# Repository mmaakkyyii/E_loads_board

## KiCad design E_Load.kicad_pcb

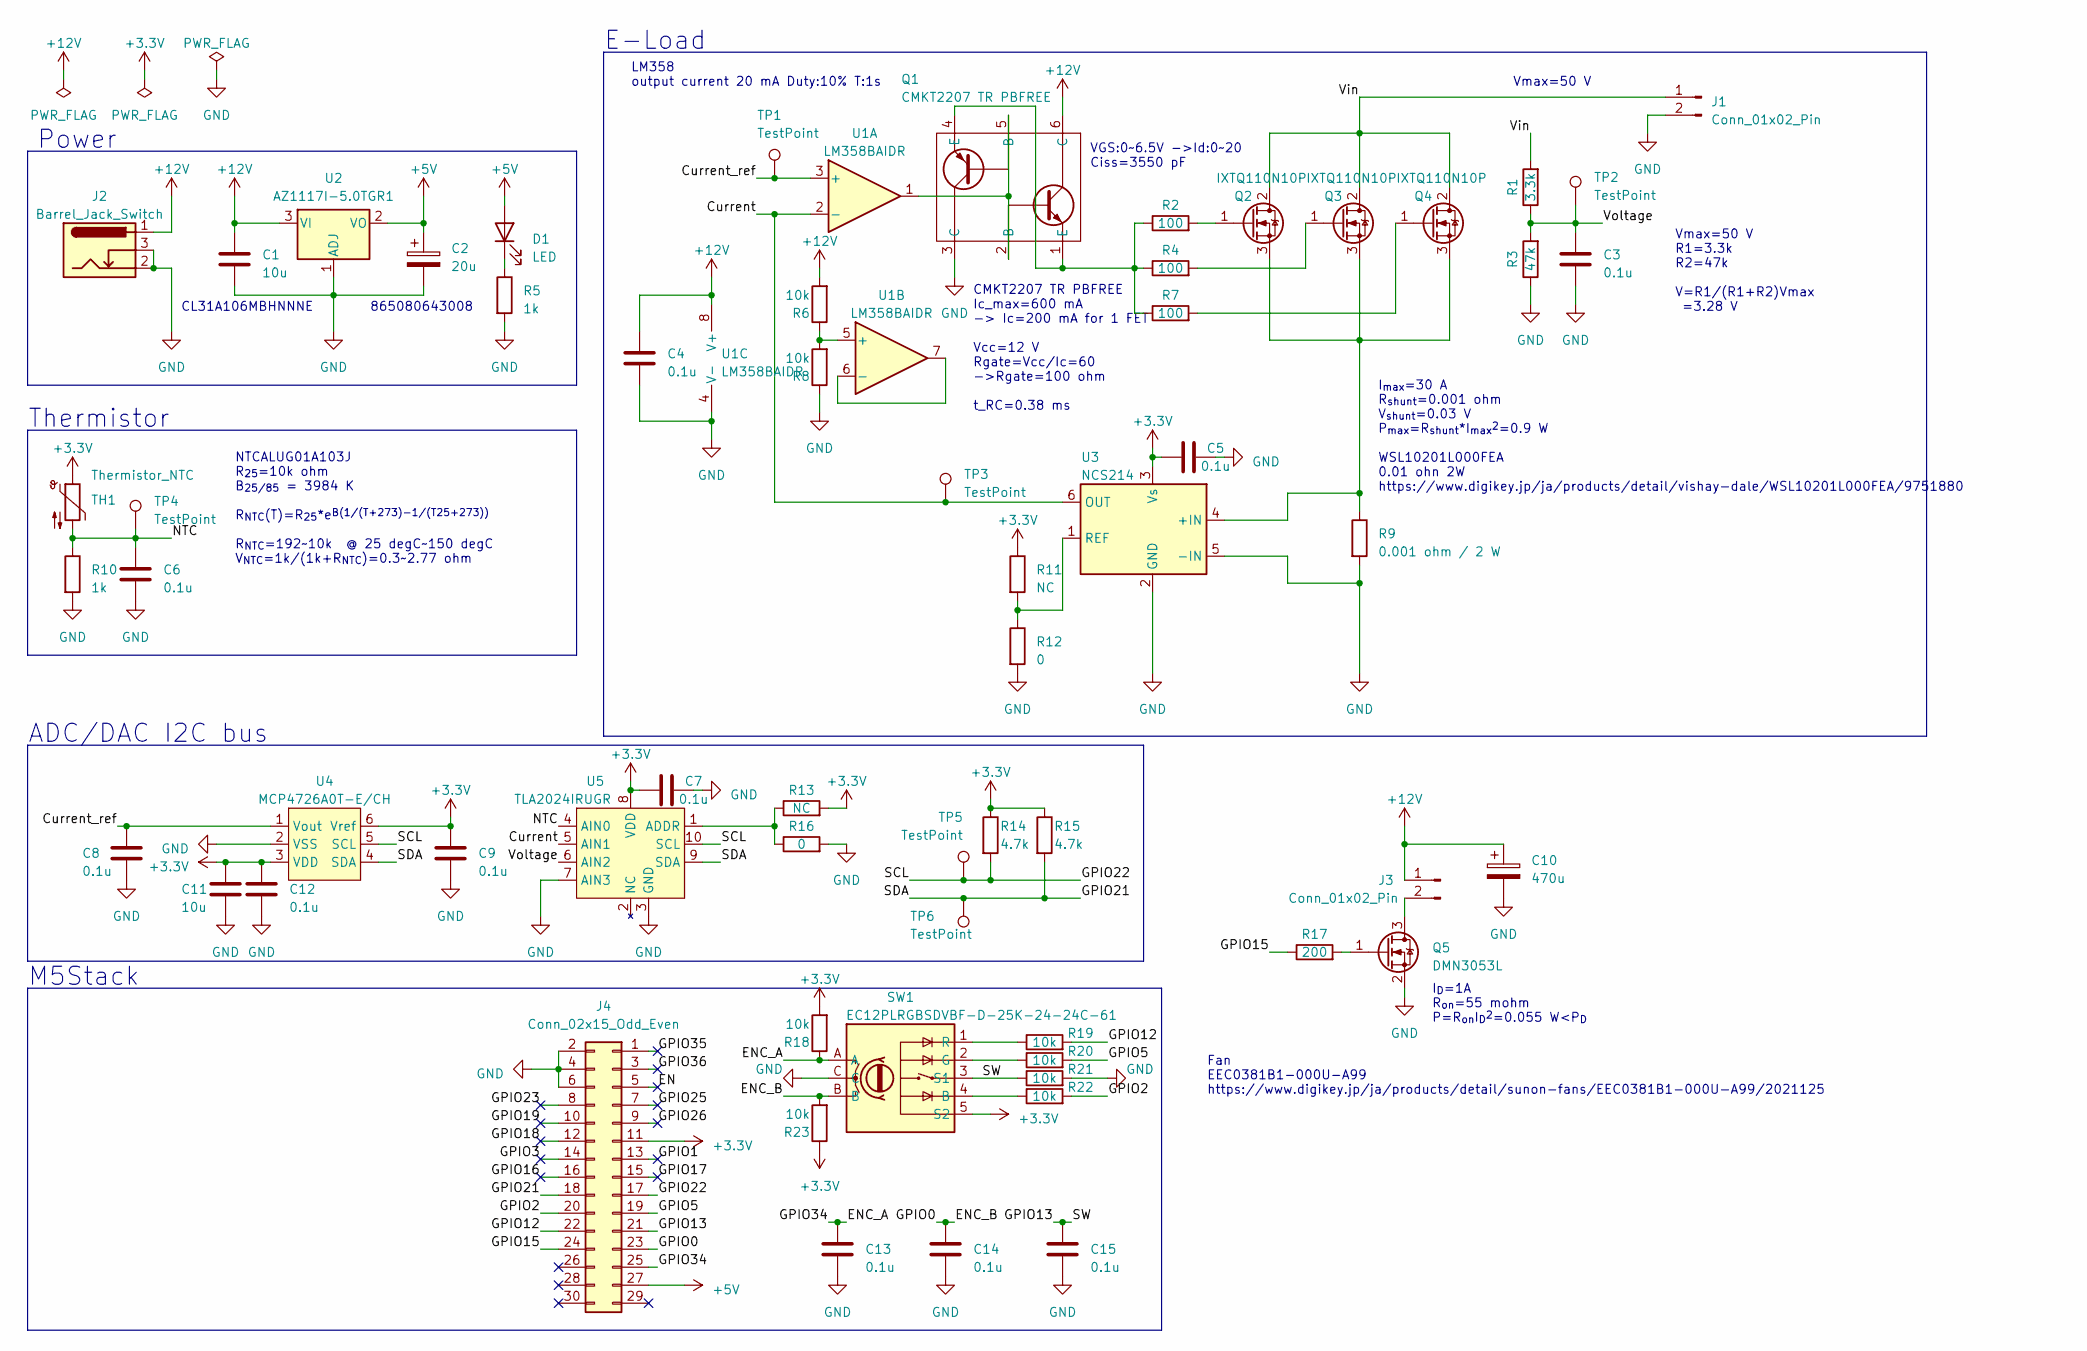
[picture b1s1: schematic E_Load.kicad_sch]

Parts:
C1, C11: 10u; C_1206_3216Metric
C2: 20u; CP_Elec_6.3x5.2
C3, C4, C5, C6, C7, C8, C9, C12, C13, C14, C15: 0.1u; C_0402_1005Metric
C10: 470u; CP_Elec_6.3x5.2
D1: LED; LED_0603_1608Metric
J1: Conn_01x02_Pin; XT30PW-M
J2: Barrel_Jack_Switch; BarrelJack_Kycon_KLDX-0202-xC_Horizontal
J3: Conn_01x02_Pin; JST_PH_B2B-PH-K_1x02_P2.00mm_Vertical
J4: Conn_02x15_Odd_Even; PinHeader_2x15_P2.54mm_Vertical
Q1: CMKT2207 TR PBFREE; SOT-363_SC-70-6
Q2, Q3, Q4: IXTQ110N10P; TO-3P-3_Horizontal_TabUp
Q5: DMN3053L; SOT-23
R1: 3.3k; R_0402_1005Metric
R2, R4, R7: 100; R_0402_1005Metric
R3: 47k; R_0402_1005Metric
R5, R10: 1k; R_0402_1005Metric
R6, R8, R18, R19, R20, R21, R22, R23: 10k; R_0402_1005Metric
R9: 0.001 ohm / 2 W; R_1020_2550Metric
R11, R13: NC; R_0402_1005Metric
R12, R16: 0; R_0402_1005Metric
R14, R15: 4.7k; R_0402_1005Metric
R17: 200; R_0402_1005Metric
SW1: EC12PLRGBSDVBF-D-25K-24-24C-61
TH1: Thermistor_NTC; R_Axial_DIN0204_L3.6mm_D1.6mm_P2.54mm_Vertical
TP1, TP2, TP3, TP4, TP5, TP6: TestPoint; TestPoint_Loop_D1.80mm_Drill1.0mm_Beaded
U1: LM358BAIDR; SOIC-8_3.9x4.9mm_P1.27mm
U2: AZ1117I-5.0TGR1; SOT-223-3_TabPin2
U3: NCS214; SOT-363_SC-70-6
U4: MCP4726A0T-E/CH; SOT-23-6
U5: TLA2024IRUGR; Texas_R-PUQFN-N10

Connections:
+3.3V: C5.1, C7.1, C9.1, C11.1, C12.1, J4.11, R11.1, R13.2, R14.1, R15.1, R18.2, R23.1, SW1.5 (S2), TH1.1, U3.3 (Vs), U4.3 (VDD), U4.6 (Vref), U5.8 (VDD)
+5V: C2.1, D1.2 (A), J4.27, U2.2 (VO)
+12V: C1.1, C4.1, C10.1, J2.1, J3.1, Q1.6 (C), R6.2, U1.8 (V+), U2.3 (VI)
/Current: TP3.1, U1.2 (-), U3.6 (OUT), U5.5 (AIN1)
/Current_ref: C8.1, TP1.1, U1.3 (+), U4.1 (Vout)
/EN: J4.5
/ENC_A: C13.1, J4.25, R18.1, SW1.A
/ENC_B: C14.1, J4.23, R23.2, SW1.B
/GPIO1: J4.13
/GPIO2: J4.20, R22.2
/GPIO3: J4.14
/GPIO5: J4.19, R20.2
/GPIO12: J4.22, R19.2
/GPIO13: C15.1, J4.21, R21.1, SW1.3 (S1)
/GPIO15: J4.24, R17.1
/GPIO16: J4.16
/GPIO17: J4.15
/GPIO18: J4.12
/GPIO19: J4.10
/GPIO21: J4.18, R15.2, TP6.1, U4.4 (SDA), U5.9 (SDA)
/GPIO22: J4.17, R14.2, TP5.1, U4.5 (SCL), U5.10 (SCL)
/GPIO23: J4.8
/GPIO25: J4.7
/GPIO26: J4.9
/GPIO35: J4.1
/GPIO36: J4.3
/NTC: C6.1, R10.1, TH1.2, TP4.1, U5.4 (AIN0)
/Vin: J1.1, Q2.2 (D), Q3.2 (D), Q4.2 (D), R1.2
/Voltage: C3.1, R1.1, R3.2, TP2.1, U5.6 (AIN2)
GND: C1.2, C2.2, C3.2, C4.2, C5.2, C6.2, C7.2, C8.2, C9.2, C10.2, C11.2, C12.2, C13.2, C14.2, C15.2, J1.2, J2.2, J2.3, J4.2, J4.4, J4.6, Q1.3 (C), Q5.2 (S), R3.1, R5.2, R8.1, R9.2, R10.2, R12.2, R16.2, R21.2, SW1.C, U1.4 (V-), U2.1 (ADJ), U3.2 (GND), U3.5 (-IN), U4.2 (VSS), U5.3 (GND), U5.7 (AIN3)
unnamed: D1.1 (K), R5.1
unnamed: J3.2, Q5.3 (D)
unnamed: Q1.2 (B), Q1.5 (B), U1.1
unnamed: Q1.1 (E), Q1.4 (E), R2.1, R4.1, R7.1
unnamed: Q2.1 (G), R2.2
unnamed: Q2.3 (S), Q3.3 (S), Q4.3 (S), R9.1, U3.4 (+IN)
unnamed: Q3.1 (G), R4.2
unnamed: Q4.1 (G), R7.2
unnamed: Q5.1 (G), R17.2
unnamed: R22.1, SW1.4 (B)
unnamed: R20.1, SW1.2 (G)
unnamed: R19.1, SW1.1 (R)
unnamed: R6.1, R8.2, U1.5 (+)
unnamed: U1.6 (-), U1.7
unnamed: R11.2, R12.1, U3.1 (REF)
unnamed: R13.1, R16.1, U5.1 (ADDR)

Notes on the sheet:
Power
E-Load
ADC/DAC I2C bus
VGS:0~6.5V ->Id:0~20 Ciss=3550 pF
CL31A106MBHNNNE
Thermistor
I_{D}=1A R_{on}=55 mohm P=R_{on}I_{D}^{2}=0.055 W<P_{D}
Vmax=50 V R1=3.3k R2=47k V=R1/(R1+R2)Vmax =3.28 V
Vmax=50 V
I_{max}=30 A R_{shunt}=0.001 ohm V_{shunt}=0.03 V P_{max}=R_{shunt}*I_{max}^{2}=0.9 W WSL10201L000FEA 0.01 ohn 2W https://www.digikey.jp/ja/products/detail/vishay-dale/WSL10201L000FEA/9751880
CMKT2207 TR PBFREE Ic_max=600 mA -> Ic=200 mA for 1 FET Vcc=12 V Rgate=Vcc/Ic=60 ->Rgate=100 ohm t_RC=0.38 ms
865080643008
Fan EEC0381B1-000U-A99 https://www.digikey.jp/ja/products/detail/sunon-fans/EEC0381B1-000U-A99/2021125
M5Stack
LM358 output current 20 mA Duty:10% T:1s
NTCALUG01A103J R_{25}=10k ohm B_{25/85} = 3984 K R_{NTC}(T)=R_{25}*e^{B(1/(T+273)-1/(T25+273))} R_{NTC}=192~10k @ 25 degC~150 degC V_{NTC}=1k/(1k+R_{NTC})=0.3~2.77 ohm

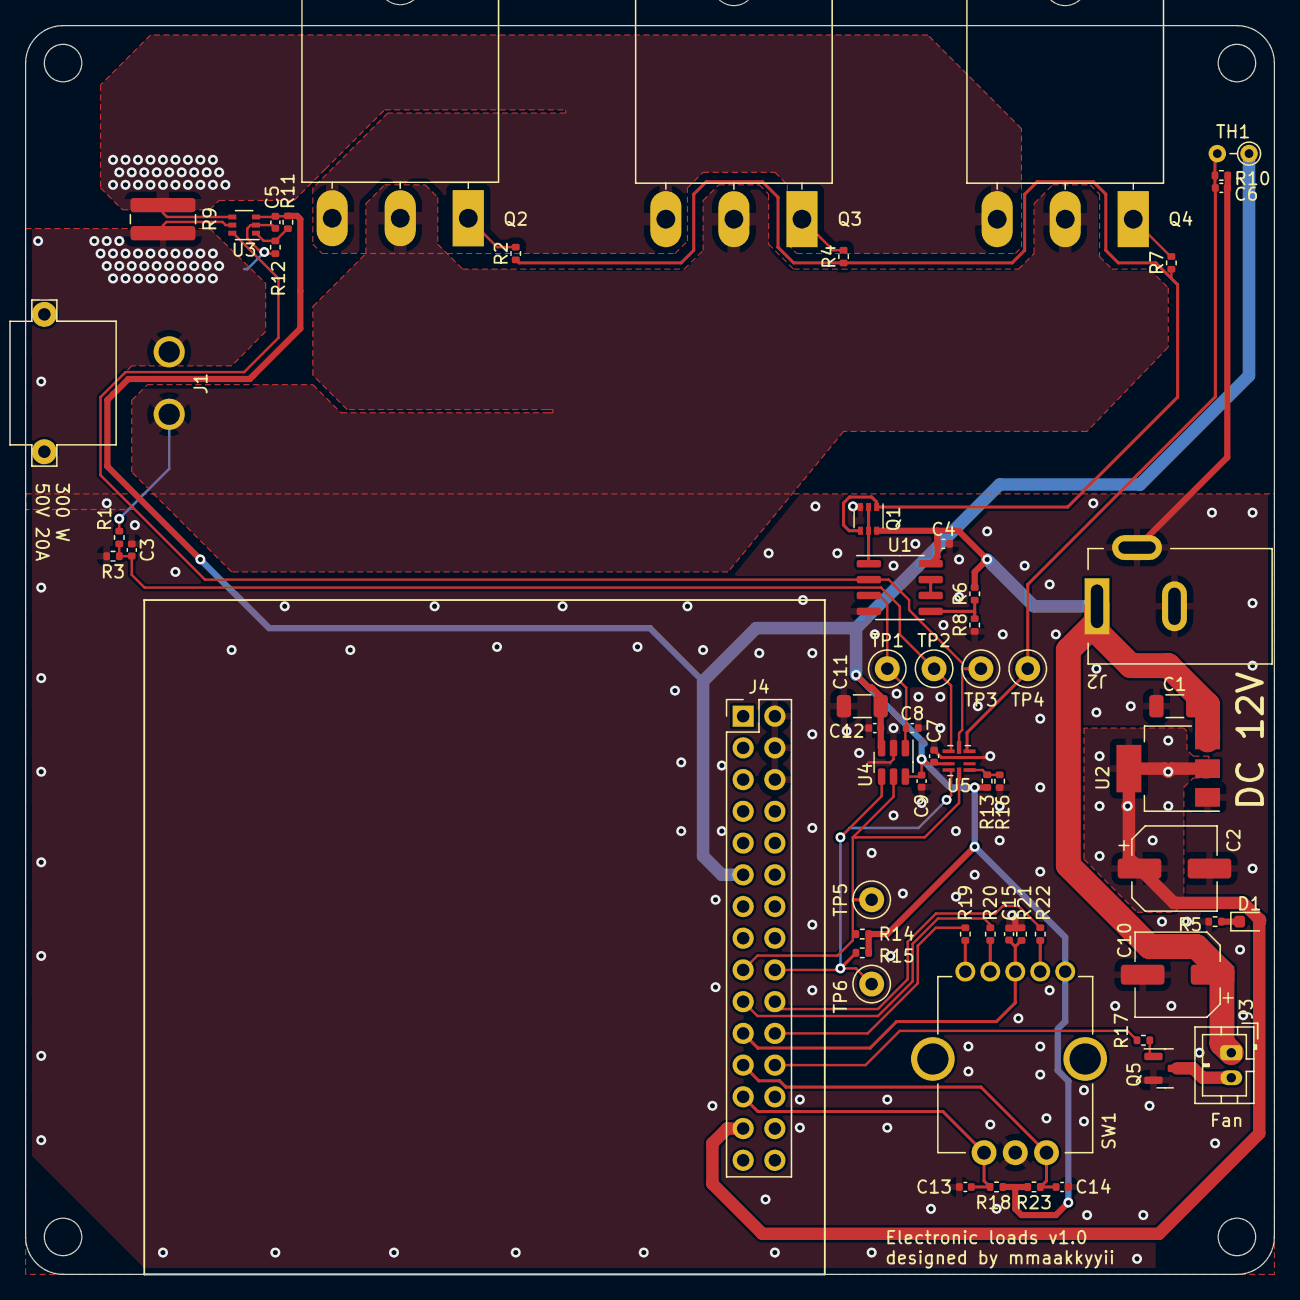
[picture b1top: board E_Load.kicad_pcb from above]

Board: 2 copper layers, 100.0 x 100.0 mm, 61 parts (0 on the bottom side), 34 nets.

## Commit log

2023-05-15 plot pdf sch
2023-06-18 v1.0
